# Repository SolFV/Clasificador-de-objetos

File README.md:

# 🏭 Clasificador Automático de Cajas con Visión Artificial
### Proyecto 4: Interfaz de Usuario y Estructura Mecánica de Cinta Transportadora

<div align="center">

**Sistema mecatrónico embebido de inspección de calidad y clasificación automatizada de paquetes sobre cinta transportadora, integrando visión artificial en la nube, tracción controlada por motor paso a paso, almacenamiento de evidencias y dashboard de supervisión en tiempo real.**

*Facultad de Ingeniería — Universidad Nacional de Asunción (FIUNA)*  
*Cátedra: Proyecto 4 (2do Ciclo 2026) | Septiembre de 2026*  
*Profesores: Prof. Ing. Federico Gaona, MSc. (Teoría) — Prof. Ing. Esteban Fretes, MSc. (Práctica)*

</div>

---

## 📋 Tabla de Contenidos

- [Descripción General](#-descripción-general)
- [Estado del Proyecto — Hitos del 1er Parcial](#-estado-del-proyecto--hitos-del-1er-parcial)
- [Esquema General del Sistema](#-esquema-general-del-sistema)
- [Arquitectura de Hardware](#️-arquitectura-de-hardware)
  - [1. Subsistema Mecánico y Estructura (SolidWorks)](#1-subsistema-mecánico-y-estructura-solidworks)
  - [2. Subsistema de Tracción (NEMA 23 + L298N)](#2-subsistema-de-tracción-nema-23--l298n)
  - [3. Subsistema Electrónico de Control (PCB ESP32-S3)](#3-subsistema-electrónico-de-control-pcb-esp32-s3)
- [Flujo de Operación y Lógica de Clasificación](#-flujo-de-operación-y-lógica-de-clasificación)
- [Infraestructura IoT y Servidor de Visión (n8n)](#-infraestructura-iot-y-servidor-de-visión-n8n)
- [Interfaz de Usuario (Dashboard de Supervisión)](#-interfaz-de-usuario-dashboard-de-supervisión)
- [Resultados Experimentales del Parcial](#-resultados-experimentales-del-parcial)
- [Costos del Proyecto](#-costos-del-proyecto)
- [Estructura del Repositorio](#-estructura-del-repositorio)
- [Autores y Agradecimientos](#-autores-fiuna--2026)
- [Licencia](#-licencia)

---

## 📖 Descripción General

El proyecto resuelve el **control de calidad en líneas de empaquetado** mediante un prototipo mecatrónico accesible y modular: una cinta transportadora desplaza cajas frente a una estación de inspección óptica (sensor infrarrojo de proximidad y cámara digital), un agente de visión artificial dictamina el estado del empaque y el sistema registra la evidencia fotográfica en la nube a la vez que acciona un mecanismo deflector para separar los productos defectuosos.

El alcance del **Primer Parcial del Proyecto 4** cierra la brecha entre la electrónica fabricada previamente en el Proyecto 3 y la operación física en planta, dotando al clasificador de:
1. **Estructura mecánica formal:** Chasis, rodillos, banda de caucho y soportes diseñados en SolidWorks con planos constructivos acotados.
2. **Tracción precisa con motor paso a paso:** Sustitución del motor DC de tracción por un motor paso a paso **NEMA 23** con controlador dedicado **L298N**, logrando un avance controlado con paradas repetibles de **1,2 s** frente a la cámara para eliminar el desenfoque por movimiento (*motion blur*).
3. **Pipeline de visión en la nube:** Servidor autoalojado **n8n** que procesa la imagen con **OpenAI `gpt-4o-mini`**, almacena evidencias en **Google Drive** y registros numéricos en **Google Sheets**.
4. **Dashboard web en tiempo real:** Interfaz de supervisión que lee la hoja de resultados cada 10 segundos, mostrando métricas, miniaturas de las cajas inspeccionadas y exportación a CSV.

---

## ✅ Estado del Proyecto — Hitos del 1er Parcial

> **El Primer Parcial del Proyecto 4 ha sido completado y validado experimentalmente con éxito en laboratorio.**

### Matriz de Hitos (P4 — Primer Parcial):

| Hito / Entregable | Estado | Observación |
| :--- | :---: | :--- |
| **Diseño mecánico en SolidWorks (CAD 3D)** | ✅ Completado | Modelos de bastidor, rodillos, engranajes y ensamble completo (`Ensamble.SLDASM`). |
| **Planos técnicos acotados de fabricación** | ✅ Completado | Planos 2D en PDF de engranaje conductor, conducido, soporte lateral y ensamble general. |
| **Tracción paso a paso NEMA 23 + L298N** | ✅ Completado | Paradas programadas de 1,2 s y avance exacto sin deslizamiento. |
| **Transmisión por engranajes rectos (3.8:1)** | ✅ Completado | Impresión 3D en PLA de piñón (z=10) y corona (z=38), módulo 4 mm. |
| **Flujo de Visión n8n + GPT-4o-mini** | ✅ Completado | Inferencia visual remota con latencia de 2,5 a 4,0 s. |
| **Registro Cloud (Google Drive + Sheets)** | ✅ Completado | Almacenamiento automático de fotos y fila de metadatos por evento. |
| **Dashboard Web de Supervisión** | ✅ Completado | Actualización continua cada 10 s, KPIs por estado, visor fotográfico y exportación CSV. |
| **Ensamble y validación del prototipo físico** | ✅ Completado | Estructura de contrachapado y varillas DIN 975 operativa y verificada en banco. |

---

## 🗺️ Esquema General del Sistema

El sistema opera mediante la interacción coordinada de cinco bloques funcionales:

```
                  +-------------------------------------------------------------+
                  |                      UNIDAD DE CONTROL                      |
                  |                Placa Propia ESP32-S3 (3.3V)                 |
                  +--------------+------------------------------+---------------+
                                 |                              |
               Señal de Detención|                              |Control de Desvío
               y Pulsos de Avance|                              |Pulsos PWM (0° / 180°)
                                 v                              v
            +--------------------+---------+          +---------+--------------------+
            |      SUBSISTEMA TRACCIÓN     |          |       SUBSISTEMA DESVÍO      |
            |     Driver L298N + NEMA 23   |          |    Servomotor SER0006        |
            |  Engranajes PLA (Red. 3.8:1) |          | Brazo Deflector (20s retenc.)|
            +--------------------+---------+          +------------------------------+
                                 |
                                 v
                     [ Cinta Transportadora ] <=== [ Cajas en Tránsito ]
                                 |
                          Detección IR (E18-D80NK)
                          Captura Foto (OV5640 SVGA)
                                 |
                                 v WiFi (HTTP POST Webhook)
            +--------------------+---------------------------------------------------+
            |                     SERVIDOR DE VISIÓN (n8n Autoalojado)               |
            |             Agente IA de Visión (OpenAI gpt-4o-mini)                  |
            +--------------------+------------------------------+--------------------+
                                 |                              |
                   Guarda Foto   v                 Guarda Fila  v
                         +-------+-------+              +-------+-------+
                         | Google Drive  |              | Google Sheets |
                         +-------+-------+              +-------+-------+
                                 |                              |
                                 |            Lectura cada 10 s |
                                 +--------------+---------------+
                                                v
                                 +--------------+---------------+
                                 |     DASHBOARD WEB (GUI)      |
                                 |  Supervisión en Tiempo Real  |
                                 +------------------------------+
```

---

## 🛠️ Arquitectura de Hardware

### 1. Subsistema Mecánico y Estructura (SolidWorks)
La cinta transportadora se diseñó íntegramente en SolidWorks bajo criterios de rigidez, repetibilidad y desmontaje modular:
- **Bastidor Lateral (`Tabla.SLDPRT` / [Soporte Lateral.pdf](Hardware/Diseno_Mecanico/Soporte%20Lateral.pdf)):** 2 placas de madera contrachapada de $700 \times 150\text{ mm}$ y $12\text{ mm}$ de espesor con perforaciones para varillas y rodamientos.
- **Tirantes Transversales (`Varilla.SLDPRT`):** 7 varillas roscadas de acero al carbono galvanizado bajo norma **DIN 975** (M6), aportando alta rigidez torsional.
- **Banda de Transporte (`Cinta.SLDPRT`):** Banda cerrada de caucho continuo con ancho útil de **200 mm**, compatible con cajas de hasta 150 mm.
- **Transmisión por Engranajes Rectos en PLA (Módulo 4 mm):**
  - **Engranaje Conductor (`Engranaje_C.SLDPRT` / [Engranaje_Conductor.pdf](Hardware/Diseno_Mecanico/Engranaje_Conductor.pdf)):** $z_1 = 10\text{ dientes}$, diámetro exterior $\varnothing 48.00\text{ mm}$, acople a eje del motor NEMA 23 de $\varnothing 8.00\text{ mm}$.
  - **Engranaje Conducido (`engranaje_G.SLDPRT` / [engranaje_conducido.PDF](Hardware/Diseno_Mecanico/engranaje_conducido.PDF)):** $z_2 = 38\text{ dientes}$, diámetro exterior $\varnothing 160.00\text{ mm}$, acople a eje motriz de $\varnothing 6.00\text{ mm}$.
  - **Relación de Reducción:** $i = 3.8:1$, cuadruplicando el par sobre el rodillo motriz y permitiendo una resolución de avance lineal de $\approx 0.165\text{ mm/paso}$.
- **Planos Técnicos:** Disponibles en [Hardware/Diseno_Mecanico/](Hardware/Diseno_Mecanico/) con el ensamble general en [Cinta transportadora.pdf](Hardware/Diseno_Mecanico/Cinta%20transportadora.pdf) y el informe técnico detallado en [Informe_Diseno_Estructural_Mecanico.md](Hardware/Diseno_Mecanico/Informe_Diseno_Estructural_Mecanico.md).

### 2. Subsistema de Tracción (NEMA 23 + L298N)
- **Motor:** Paso a paso híbrido bipolar NEMA 23 (**modelo 23HS5628**), ángulo de paso $1.8^\circ$ (200 pasos/rev) y torque nominal de **12.6 kgf-cm** (1.23 N·m).
- **Controlador:** Driver tipo puente H bipolar **L298N**, alimentado desde una línea de potencia externa dedicada y comandado por señales lógicas de 3.3V desde la placa ESP32-S3.

### 3. Subsistema Electrónico de Control (PCB ESP32-S3)
Se reutiliza la placa desarrollada y validada en el Proyecto 3 (alojada en [Hardware/Diseño final p3/](Hardware/Diseño%20final%20p3/)):
- **Microcontrolador:** ESP32-S3-WROOM-1-N16R8 (Dual-core 240 MHz, 16 MB Flash, 8 MB PSRAM verificada).
- **Cámara Óptica:** Módulo digital Omnivision **OV5640** conectado mediante interfaz de video en paralelo DVP (resolución de trabajo SVGA $800 \times 600$).
- **Sensor de Presencia:** Sensor fotoeléctrico infrarrojo **E18-D80NK** enfocado a la zona de captura (tiempo de respuesta $< 50\text{ ms}$).
- **Actuador de Desvío:** Servomotor **DFRobot SER0006** montado con brazo deflector mecánico a la salida del tramo de inspección.

---

## 🔄 Flujo de Operación y Lógica de Clasificación

El lazo de control opera de acuerdo a la siguiente secuencia automática:

1. **Avance Continuo:** El motor NEMA 23 hace avanzar la cinta transportadora de manera uniforme.
2. **Detección Frontal:** El sensor infrarrojo E18-D80NK detecta la llegada del paquete e interrumpe el avance.
3. **Parada y Captura:** La cinta se detiene exactamente durante **1,2 segundos**. La cámara OV5640 toma una fotografía nítida en SVGA almacenándola en la PSRAM.
4. **Transmisión IoT:** El ESP32-S3 envía la imagen por WiFi al webhook de n8n mediante HTTP POST.
5. **Inferencia Visual:** El agente de IA (`gpt-4o-mini`) analiza la morfología y condiciones del empaque, dictaminando la categoría:
   - 🟢 **Verde (Buen Estado):** Caja intacta, correctamente sellada y lista para despacho.
   - 🟡 **Amarillo (Sin Caja o No Empaque):** Falsa alarma, objeto extraño o cinta vacía.
   - 🔴 **Rojo (Caja Dañada):** Paquete aplastado, roto, perforado o con defectos visibles.
6. **Almacenamiento Cloud:** El flujo guarda la imagen en una carpeta compartida de **Google Drive** y registra una nueva fila en **Google Sheets** con timestamp, color y descripción detallada.
7. **Acción del Servomotor:** El ESP32-S3 recibe la respuesta `[{color, descripcion}]` y ejecuta la maniobra:
   - 🟢 **Verde:** El brazo deflector permanece a **0°** (la caja continúa sin desvío).
   - 🟡 / 🔴 **Amarillo o Rojo:** El servomotor gira a **180°** y mantiene la posición de desvío durante **20 segundos** para enviar la pieza a la bandeja de rechazo.
8. **Reanudación:** El servomotor retorna a posición neutra (0°) y la cinta reanuda la marcha.

---

## 🤖 Infraestructura IoT y Servidor de Visión (n8n)

El procesamiento cognitivo se delega íntegramente a un servidor local **n8n autoalojado** (*Workflow Proyecto 4*):

```
[Webhook HTTP] ──▶ [Recibir imagen y Nombrar] ──▶ [Base64 a Binario] ──▶ [AI Agent (gpt-4o-mini)]
                                                                                │
[Responder al Webhook: {color, desc}] ◀── [Limpiar Output Agente] ◀─────────────┘
          │
          ├──▶ [Subir a Google Drive]
          └──▶ [Subir a Google Sheets]
```

- **Modelo de Inferencia:** OpenAI `gpt-4o-mini` configurado con *system prompt* especializado en control de calidad industrial.
- **Respuesta JSON:** Formato estandarizado `[ { "color": "verde" | "amarillo" | "rojo", "descripcion": "..." } ]`.
- **Ventaja de la Arquitectura:** Libera al microcontrolador de tareas pesadas de redes neuronales, acelerando la toma de decisiones ($2.5 - 4.0\text{ s}$).

---

## 🖥️ Interfaz de Usuario (Dashboard de Supervisión)

El monitoreo del sistema se realiza a través de un **Dashboard Web en Tiempo Real** de un solo archivo:
- **Consulta Automática:** Sondea la planilla de Google Sheets (*Proyecto4 - Hoja 1*) cada **10 segundos**.
- **Panel de KPIs:** Conteo total de cajas evaluadas, desglose por categoría (verde, amarillo, rojo) y cálculo porcentual.
- **Tarjeta de Última Detección:** Muestra la fotografía en miniatura cargada desde Google Drive, el estado asignado, la descripción diagnóstica de la IA y el ángulo/tiempo aplicado por el servomotor.
- **Historial y Exportación:** Tabla con las últimas 5 detecciones en vivo y botón para exportar todo el registro histórico acumulado a formato **CSV**.
- **Accesos Directos:** Enlaces directos a la planilla en línea y a la carpeta de evidencias en Drive.
- **Modo Seguro:** Opera en modo solo lectura para supervisión remota sin interferir en la máquina de estados del firmware.

---

## 📊 Resultados Experimentales del Parcial

Durante las pruebas funcionales del prototipo integrado se validaron las siguientes métricas de desempeño:

| Parámetro Operativo | Valor Medido | Valor Esperado / Criterio |
| :--- | :---: | :---: |
| **Tiempo de parada de cinta frente a cámara** | **1,2 s** | Repetible, sin desenfoque de imagen |
| **Latencia de detección del sensor IR** | **< 50 ms** | Detención instantánea del NEMA 23 |
| **Tiempo de respuesta inferencia n8n** | **2,5 a 4,0 s** | Dentro del ciclo de cinta previsto |
| **Retención del servomotor en rechazo (180°)** | **20 s** | Desvío seguro al contenedor de descarte |
| **Frecuencia de actualización del Dashboard** | **10 s** | Supervisión fluida de métricas Cloud |
| **Resolución cinemática de la cinta** | **~0,165 mm/paso** | Posicionamiento milimétrico repetible |

---

## 💰 Costos del Proyecto

La estructura de costos del prototipo se basa en una tasa oficial de referencia de **1 USD = 6.391 Gs.**:

### 1. Materiales y Herramientas Compradas (Incorporadas al Proyecto 4)

| Descripción / Componente | MPN / Modelo | Cant. | Unitario (USD) | Total (USD) | Total (Gs.) |
| :--- | :--- | :---: | :---: | :---: | :---: |
| **Motor paso a paso NEMA 23 (12.6 kgf-cm)** | 23HS5628 | 1 | 46,94 | 46,94 | 300.000 |
| **Microcontrolador ESP32-S3** | ESP32-S3-WROOM-1-N16R8 | 2 | 8,72 | 17,44 | 111.459 |
| **Módulo de cámara OV5640** | 5840 (Adafruit) | 1 | 9,95 | 9,95 | 63.590 |
| **Capacitor electrolítico 100 uF** | EEE-FK1H101P | 6 | 0,76 | 4,56 | 29.143 |
| **Servomotor 180°** | SER0006 | 1 | 3,63 | 3,63 | 23.199 |
| **Capacitor cerámico 4,7 uF 0805** | CL21B475KOFNNNE | 6 | 0,25 | 1,50 | 9.587 |
| **Diodo Schottky 40 V, 1 A** | SS14F-HF | 4 | 0,32 | 1,28 | 8.180 |
| **Conector USB tipo C hembra** | USB4510-03-1-A | 1 | 0,84 | 0,84 | 5.368 |
| **Capacitor cerámico 10 uF 0805** | CL21B106KOQNNNE | 6 | 0,14 | 0,84 | 5.368 |
| **Capacitor cerámico 22 uF 0805** | CL21A226MQQNNNE | 6 | 0,13 | 0,78 | 4.985 |
| **Resistencia 15 kOhm 0805** | RC0805FR-0715KL | 6 | 0,13 | 0,78 | 4.985 |
| **Capacitor cerámico 2,2 uF 0805** | CL21B225KOFNNNE | 6 | 0,12 | 0,72 | 4.602 |
| **Regulador LDO 3,3 V** | LD1117S33TR | 2 | 0,34 | 0,68 | 4.346 |
| **Resistencia 10 kOhm 0805** | RC0805FR-0710KL | 6 | 0,11 | 0,66 | 4.218 |
| **Capacitores y Resistencias SMD 0805 varios** | Pasivos estándar | — | — | 6,14 | 39.299 |
| **SUBTOTAL COMPONENTES COMPRADOS** | — | — | — | **$96,06** | **644.219 Gs.** |

> *Costo por integrante (3 personas): **$32.02 USD (214.740 Gs.)**.*  
> El desglose línea a línea con enlaces y números de parte se encuentra en el archivo [BOM.csv](BOM.csv).

### 2. Materiales y Herramientas Preexistentes o Prestadas (Sin costo incremental)

| Descripción | Cantidad | Observaciones / Procedencia |
| :--- | :---: | :--- |
| **Placa propia ESP32-S3 con cámara OV5640** | 1 | Fabricada y validada en Proyecto 3 |
| **Servomotor de desvío SER0006** | 1 | Reutilizado de la etapa previa |
| **Controlador L298N para motor paso a paso** | 1 | Driver provisto para tracción |
| **Notebook con servidor n8n autoalojado** | 1 | Estación de inferencia local |
| **Licencia / estación SolidWorks CAD** | 1 | Laboratorio FIUNA |
| **Multímetro y herramientas de banco/taller** | 1 | Instrumental de ensamblaje y prueba |

---

## 📁 Estructura del Repositorio

```
📦 Clasificador de Objetos/
├── 📂 Hardware/                                # Proyectos de diseño físico y electrónico
│   ├── 📂 Diseno_Mecanico/                     # Diseño mecánico CAD y planos (P4)
│   │   ├── 📄 Informe_Diseno_Estructural_Mecanico.md # Informe técnico mecánico detallado
│   │   ├── 📄 Cinta transportadora.pdf         # Plano de ensamble general, despiece y lista de partes
│   │   ├── 📄 Soporte Lateral.pdf              # Plano acotado de soporte lateral de madera contrachapada
│   │   ├── 📄 Engranaje_Conductor.pdf          # Plano acotado de engranaje conductor (z=10, m=4)
│   │   ├── 📄 engranaje_conducido.PDF          # Plano acotado de engranaje conducido (z=38, m=4)
│   │   ├── 🧊 Ensamble.SLDASM                  # Ensamblaje 3D general en SolidWorks
│   │   ├── 🧊 Cinta.SLDPRT                     # Modelo 3D de la banda transportadora
│   │   ├── 🧊 Engranaje_C.SLDPRT               # Modelo 3D de engranaje conductor (PLA)
│   │   ├── 🧊 engranaje_G.SLDPRT               # Modelo 3D de engranaje conducido (PLA)
│   │   ├── 🧊 Tabla.SLDPRT                     # Modelo 3D de soporte lateral
│   │   ├── 🧊 Varilla.SLDPRT                   # Modelo 3D de varilla roscada DIN 975
│   │   └── 🧊 nema23.SLDPRT                    # Modelo 3D de motor paso a paso NEMA 23
│   ├── 📂 Componentes/                         # Bibliotecas KiCad personalizadas
│   ├── 📂 Diseño final p3/                     # Proyecto final KiCad de la PCB (Proyecto 3)
│   │   └── 📂 Grupo15/                         # Esquemático, ruteado, producción y Gerbers
│   ├── 📂 ESP32_S3_WROOM2_N32R16_29/           # Footprint y símbolo de la MCU
│   ├── 🖼️ Diseño.jpeg                          # Esquemático general del circuito
│   ├── 🖼️ pcb_ruteado.PNG                       # Ruteado y layout de 2 capas
│   ├── 🖼️ pcb_3d.PNG                           # Render 3D superior de la PCB
│   ├── 🖼️ pcb_3d_1.png                         # Render 3D superior sin componentes
│   └── 🖼️ pcb_3d_vistinferior.png              # Render 3D inferior de la PCB
├── 📂 Software/                                # Firmware y aplicaciones de control
│   ├── 📄 P3_2P_code.txt                       # Firmware C++/Arduino para ESP32-S3
│   ├── 📂 SnapshotP4.0/                        # Aplicación Android para inspección
│   │   └── 📱 Cinta IA.apk                     # Instalador ejecutable Android
│   └── 📂 Pruebas/                             # Scripts de validación de cámara y PSRAM
├── 📄 BOM.csv                                  # Lista de materiales y costos actualizada (USD / Gs.)
├── 📄 Informe_finalP3.pdf                      # Informe oficial completo del Proyecto 3
├── 📄 Cronograma de actividades P4.pdf         # Cronograma oficial de la Etapa P4 (PDF)
├── 📊 Cronograma de actividades.xlsx           # Planilla Excel de seguimiento
├── 🖼️ DiagramadeGantt.png                     # Diagrama de Gantt oficial
├── 🖼️ diagrama-flujo.png                       # Diagrama de flujo general del sistema
├── 📄 LICENSE                                  # Licencia de código abierto MIT
└── 📄 README.md                                # Documentación principal del repositorio
```

---

## 👥 Autores (FIUNA — 2026)

* **José Fabián Medina Dávalos** — [jfmedina@fiuna.edu.py](mailto:jfmedina@fiuna.edu.py)
* **Sol Aramí Fernández Vargas** — [solfernandez@fiuna.edu.py](mailto:solfernandez@fiuna.edu.py)
* **Gabriela Belén Orrego Arzamendia** — [gorrego@fiuna.edu.py](mailto:gorrego@fiuna.edu.py)

**Facultad de Ingeniería — Universidad Nacional de Asunción (FIUNA)**  
*Cátedra de Proyecto 4 — Carrera de Ingeniería Mecatrónica*  
*Docentes:* Prof. Ing. Federico Gaona, MSc. (Teoría) & Prof. Ing. Esteban Fretes, MSc. (Práctica)

---

## 📄 Licencia

Este proyecto está distribuido bajo la **Licencia MIT**. Para más detalles, consulte el archivo [LICENSE](LICENSE).

---

<div align="center">

*Clasificador Automático de Cajas con Visión Artificial — FIUNA — 2026*

</div>

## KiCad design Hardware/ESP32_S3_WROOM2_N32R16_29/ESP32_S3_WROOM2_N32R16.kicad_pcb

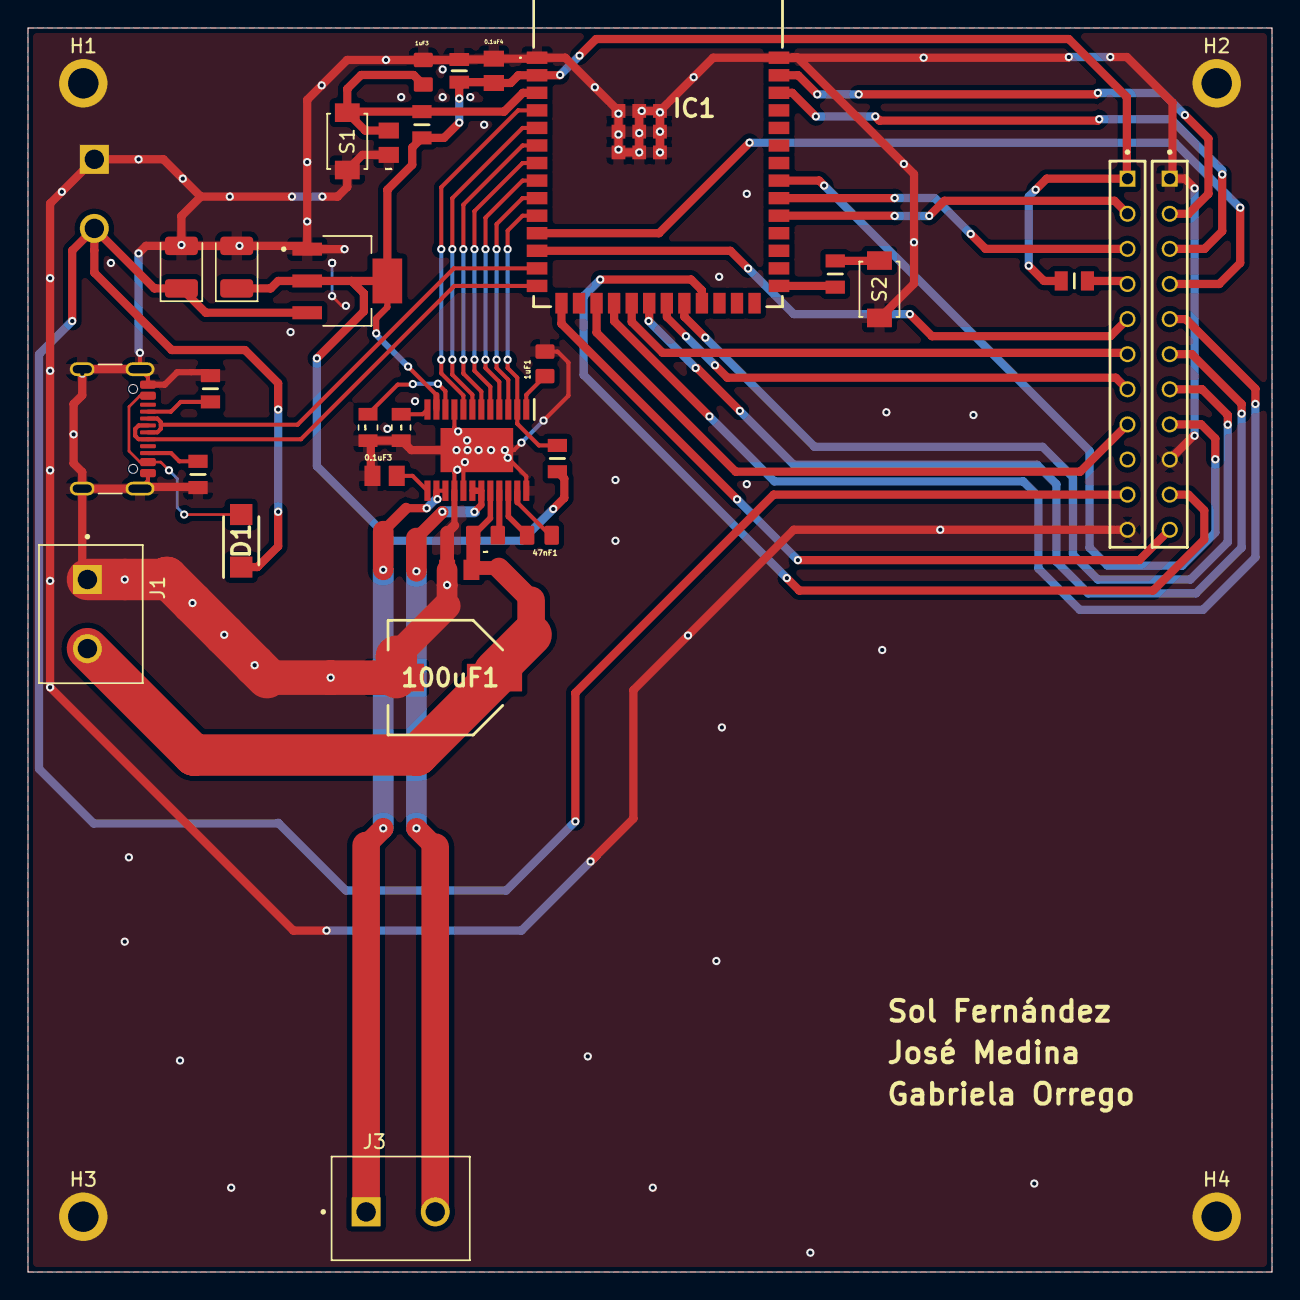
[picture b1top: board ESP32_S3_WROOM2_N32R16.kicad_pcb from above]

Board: 2 copper layers, 90.0 x 90.0 mm, 36 parts (1 on the bottom side), 44 nets.

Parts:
0.1k1: RC0805FR-07100RL; RESC2012X60N
0.1uF1, 0.1uF2, 0.1uF3, 0.1uF4: 08055C104KAT2A; CAPC2012X94N
1.5k1, 1.5k2: RC0805FR-071K5L; RESC2012X60N
1uF1, 1uF2, 1uF3: CL21B105KAFNNNE; CAPC2012X135N
5.1k1, 5.1k2: RK73H2ATTD5101F; RESC2012X60N
10k1, 10k2, 10k3: RC0805FR-0710KL; RESC2012X60N
22uF1: CL21A226MQQNNNE; CAPC2012X140N
47nF1: CL21B473KBCNNNC; CAPC2012X95N
100uF1: EEE-FK1H101P; EEHZT1E331UP
C1, C2: 10uF; CP_EIA-3528-21_Kemet-B
D1: SS14F-HF; SODFL4626X120N
H1, H2, H3, H4: MountingHole_2.2mm_M2_ISO7380_Pad
H1#2: DRV8873SPWPRQ1; SOP65P640X120-25N
IC1: ESP32-S3-WROOM-2-N32R16V; ESP32S3WROOM2N32R16V
J1, J2, J3: KF301-2P; HANDSON_KF301-2P
J4, J5: TS-111-T-A-1; SAMTEC_TS-111-T-A-1
S1, S2: TS-1088-AR02016; SW_TS-1088-AR02016
USB1: USB_C_Receptacle_USB2.0_16P; USB_C_Receptacle_GCT_USB4105-xx-A_16P_TopMnt_Horizontal
VR1: LM1117MPX-3.3_NOPB; VREG_LM1117MPX-3.3_NOPB

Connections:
+3V3: 0.1uF4.2, 10k1.2, 10k2.2, 10k3.2, 22uF1.2, C2.1, H1#2.11 (NSLEEP), IC1.2 (3V3), J5.01, VR1.2 (VOUT_2), VR1.4 (VOUT_4)
+5V: C1.1, D1.1 (K), J2.2, J5.10, VR1.3 (VIN)
BOOT: 0.1k1.1, IC1.27 (IO0)
D+: IC1.14 (IO20), USB1.A6 (D+), USB1.B6 (D+)
D-: IC1.13 (IO19), USB1.A7 (D-), USB1.B7 (D-)
EN: 0.1uF1.1, 1uF3.2, 10k2.1, IC1.3 (EN), S1.1
GND: 0.1uF1.2, 0.1uF2.1, 0.1uF3.1, 0.1uF4.1, 1.5k1.1, 1.5k2.1, 1uF1.2, 1uF3.1, 5.1k1.2, 5.1k2.2, 22uF1.1, 100uF1.2 (-), C1.2, C2.2, H1.1, H1#2.9 (DISABLE), H1#2.16 (SRC_1), H1#2.17 (SRC_2), H1#2.24 (GND), H1#2.25 (EP), H2.2, H3.3, H4.4, IC1.1 (GND_1), IC1.40 (GND_2), IC1.41 (GND_3), IC1.42 (GND_4), IC1.43 (GND_5), IC1.44 (GND_6), IC1.45 (GND_7), IC1.46 (GND_8), IC1.47 (GND_9), IC1.48 (GND_10), IC1.49 (GND_11), J1.1, J2.1, J4.01, J4.09, J5.11, S1.2, S2.2, USB1.A1 (GND), USB1.A12 (GND), USB1.B1 (GND), USB1.B12 (GND), USB1.SH (SHIELD), VR1.1 (GND)
GPIO01: IC1.39 (IO1), J4.02
GPIO02: IC1.38 (IO2), J4.03
GPIO03: IC1.15 (IO3), J4.11
GPIO04: H1#2.8 (PH/IN2), IC1.4 (IO4)
GPIO05: H1#2.7 (EN/IN1), IC1.5 (IO5)
GPIO06: H1#2.6 (NSCS), IC1.6 (IO6)
GPIO07: H1#2.5 (SCLK), IC1.7 (IO7)
GPIO08: IC1.12 (IO8), J5.05
GPIO09: IC1.17 (IO9), J5.08
GPIO10: IC1.18 (IO10), J4.05
GPIO11: IC1.19 (IO11), J5.06
GPIO12: IC1.20 (IO12), J4.06
GPIO13: IC1.21 (IO13), J5.07
GPIO14: IC1.22 (IO14), J4.07
GPIO15: H1#2.4 (SDI), IC1.8 (IO15)
GPIO16: H1#2.3 (SDO), IC1.9 (IO16)
GPIO17: 10k1.1, H1#2.2 (NFAULT), IC1.10 (IO17)
GPIO18: IC1.11 (IO18), J4.04
GPIO21: IC1.23 (IO21), J4.10
GPIO38: IC1.31 (IO38), J5.02
GPIO39: IC1.32 (IO39), J5.03
GPIO40: IC1.33 (IO40), J4.08
unnamed: 0.1k1.2, S2.1
unnamed: 10k3.1, J5.04
unnamed: D1.2 (A), USB1.A4 (VBUS), USB1.A9 (VBUS), USB1.B4 (VBUS), USB1.B9 (VBUS)
unnamed: 47nF1.2, H1#2.22 (CPH)
unnamed: 47nF1.1, H1#2.23 (CPL)
unnamed: 1uF1.1, H1#2.1 (DVDD)
unnamed: 1.5k2.2, H1#2.10 (IPROPI1)
unnamed: 1.5k1.2, H1#2.12 (IPROPI2)
unnamed: 1uF2.2, H1#2.21 (VCP)
unnamed: 0.1uF3.2, H1#2.13 (VM_1)
unnamed: 5.1k2.1, USB1.A5 (CC1)
unnamed: 5.1k1.1, USB1.B5 (CC2)
O1: H1#2.18 (OUT1_1), H1#2.19 (OUT1_2), J3.2
O2: H1#2.14 (OUT2_1), H1#2.15 (OUT2_2), J3.1
VM: 0.1uF2.2, 1uF2.1, 100uF1.1 (+), H1#2.20 (VM_2), J1.2

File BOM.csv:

,,,,,,,,
,,,,Dolar,6538,,,
,Total,414.434,Individual,138.145,,,,
,Categoría,Componente,Marca,Precio USD,Precio PYG,Link,Cant. Mín,Precio Final PYG
,MCU,ESP32-S3-WROOM-2-N32R16V,Espressif Systems,"11,40",74.533,https://www.mouser.com/ProductDetail/Espressif-Systems/ESP32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,1,74.533
,MOTOR,"NOVAMAX-6V-5,75A-800RPM",Sumozade,"15,00",98.070,https://sumozade.com/novamax-6v-800rpm-dc-motor,1,98.070
,LDO,LM1117MPX-3.3/NOPB,Diodes Incorporated,"1,04",6.800,https://www.mouser.com/ProductDetail/Texas-Instruments/LM111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,2,13.599
,DRIVER,DRV8873SPWPRQ1,Texas Instruments,"4,13",27.002,https://www.mouser.com/ProductDetail/Texas-Instruments/DRV88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,2,54.004
,CAMERA, OV5640 DVP,CN,"10,04",64.789,https://es.aliexpress.com/item/1005004471654205.html?dp=gx-r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,2,129.578
,USB-C,USB TIPO C HEMBRA 16 PINES 1.6MM SMD,Plett,"2,30",15.037,CONECTOR USB TIPO C HEMBRA 16 PINES 1.6MM SMD - Electronica Plett,1,15.037
,COMPONENTES,,,,,,,
,Capacitor de Tantalio 10uF,T491B106K016AT,KEMET,"0,44",2.877,https://www.mouser.com/ProductDetail/KEMET/T491B106K016AT?qs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,2,5.753
,Capacitor Ceramico 1uF,CL21B105KAFNNNE,Samsung Electro-Mechanics,"0,11",719,https://www.mouser.com/ProductDetail/Samsung-Electro-Mechani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,2,1.438
,"Capacitor Ceramico 0,1uF",08055C104KAT2A,KYOCERA AVX,"0,13",850,https://www.mouser.com/ProductDetail/KYOCERA-AVX/08055C104KA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,2,1.700
,Capacitor Ceramico 22uF,CL21A226MQQNNNE,Samsung Electro-Mechanics,"0,13",839,https://www.mouser.com/ProductDetail/Samsung-Electro-Mechani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,2,1.679
,Resistencia 10k 0805,RC0805FR-0710KL,YAGEO,"0,14",915,https://www.mouser.com/ProductDetail/YAGEO/RC0805FR-0710KL?q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,2,1.831
,"Resistencia 5,1k 0805",RK73H2ATTD5101F,KOA Speer,"0,10",646,https://www.mouser.com/ProductDetail/KOA-Speer/RK73H2ATTD510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,4,2.582
,"Resistencia 0,1k 0805",RC0805FR-07100RL,YAGEO,"0,10",654,https://www.mouser.com/ProductDetail/YAGEO/RC0805FR-07100RL?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,2,1.308
,Capacitor Ceramico 47nF,CL21B473KBCNNNC,Samsung Electro-Mechanics,"0,10",646,https://www.mouser.com/ProductDetail/Samsung-Electro-Mechani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,2,1.291
,Capacitor Electrolitico 100uF,EEE-FK1H101P,Panasonic,"0,72",4.707,https://www.mouser.com/ProductDetail/Panasonic/EEE-FK1H101P?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,2,9.415
,"Resistencia 1,5k 0805",RC0805FR-071K5L,YAGEO,"0,10",654,https://www.mouser.com/ProductDetail/YAGEO/RC0805FR-071K5L?q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,4,2.615

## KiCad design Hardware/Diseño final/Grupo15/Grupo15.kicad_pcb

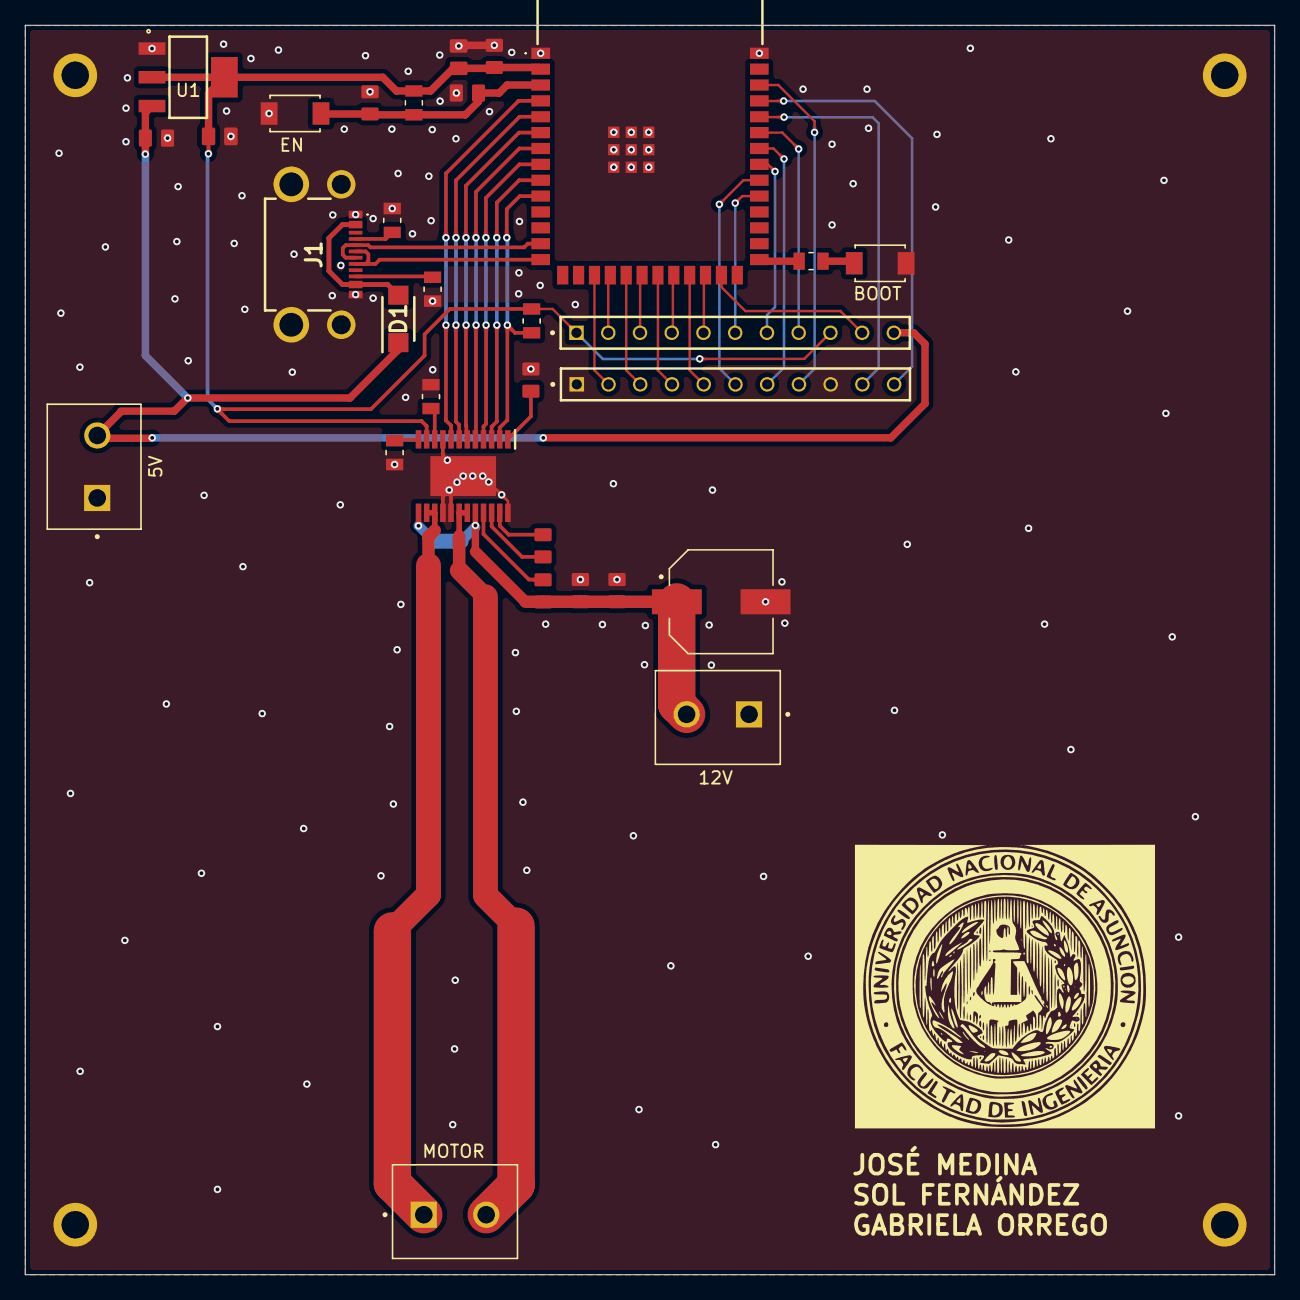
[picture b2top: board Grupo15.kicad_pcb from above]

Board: 2 copper layers, 100.0 x 100.0 mm, 35 parts (0 on the bottom side), 44 nets.

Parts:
5V, 12V: KF301-2P; HANDSON_KF301-2P
BOOT: TS-1088-AR02016; SW_TS-1088-AR02016
C1, C3, C4, C10, C11: CL21B104KBCNNNC; CAPC2012X95N
C2: CL21B106KOQNNNE; CAPC2012X140N
C5: CL21A226MQQNNNE; CAPC2012X140N
C6, C7, C9: CL21B105KAFNNNE; CAPC2012X135N
C8: CL21B473KBCNNNC; CAPC2012X95N
C12: EEEFK1H101P; CAP_EEEFK1H101P
D1: SS14F-HF; SODFL4626X120N
EN: TS-1088-AR02016; SW_TS-1088-AR02016
H1, H2, H3, H4: MountingHole_2.2mm_M2_ISO7380_Pad
H1#2: DRV8873SPWPRQ1; SOP65P640X120-25N
IC1: ESP32-S3-WROOM-1-N16R8; ESP32S3WROOM1N16R8
J1: USB4510-03-1-A; USB4510031A
J5, J6: TS-111-T-A-1; SAMTEC_TS-111-T-A-1
MOTOR: KF301-2P; HANDSON_KF301-2P
R1: RC0805FR-07100RL; RESC2012X60N
R2, R5: RC0805FR-0710KL; RESC2012X60N
R3, R4: RC0805FR-075K1L; RESC2012X60N
R6, R7: RC0805FR-071K5L; RESC2012X60N
U1: LD1117S33TR; SOT230P700X180-4N

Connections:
+3V3: C2.1, C4.1, C5.1, H1#2.11 (NSLEEP), IC1.2 (3V3), J5.01, J5.09, R2.2, R5.1, U1.2 (OUT), U1.4 (OUT)
+5V: 5V.2, C1.1, D1.1 (K), J5.11, U1.3 (IN)
BOOT: IC1.27 (IO0), R1.1
D2: IC1.38 (IO2), J6.08
D3: IC1.35 (IO42), J5.08
D4: IC1.34 (IO41), J6.07
D5: IC1.33 (IO40), J5.07
D6: IC1.32 (IO39), J6.06
D7: IC1.31 (IO38), J5.06
D8: IC1.23 (IO21), J6.05
D9: IC1.24 (IO47), J5.05
EN: C3.1, C6.1, EN.1, IC1.3 (EN), R2.1
GND: 5V.1, 12V.1, BOOT.2, C1.2, C2.2, C3.2, C4.2, C5.2, C6.2, C7.1, C10.2, C11.2, C12.2, EN.2, H1.1, H1#2.9 (DISABLE), H1#2.16 (SRC_1), H1#2.17 (SRC_2), H1#2.24 (GND), H1#2.25 (EP), H2.1, H3.1, H4.1, IC1.1 (GND_1), IC1.40 (GND_2), IC1.41 (GND_3), IC1.42 (GND_4), IC1.43 (GND_5), IC1.44 (GND_6), IC1.45 (GND_7), IC1.46 (GND_8), IC1.47 (GND_9), IC1.48 (GND_10), IC1.49 (GND_11), J1.A1 (GND_1), J1.A12 (GND_2), J1.MH1, J1.MH2, J1.MH3, J1.MH4, J6.01, J6.09, R3.1, R4.2, R6.1, R7.1, U1.1 (GND)
GPIO-04: H1#2.8 (PH/IN2), IC1.4 (IO4)
GPIO-05: H1#2.7 (EN/IN1), IC1.5 (IO5)
GPIO-06: H1#2.6 (NSCS), IC1.6 (IO6)
GPIO-07: H1#2.5 (SCLK), IC1.7 (IO7)
GPIO-15: H1#2.4 (SDI), IC1.8 (IO15)
GPIO-16: H1#2.3 (SDO), IC1.9 (IO16)
GPIO-17: H1#2.2 (NFAULT), IC1.10 (IO17), R5.2
GPIO-48: IC1.25 (IO48), J5.10
GPIO-RX: IC1.36 (RXD0), J6.10
GPIO-TX: IC1.37 (TXD0), J6.11
HS: IC1.19 (IO11), J6.03
unnamed: D1.2 (A), J1.A4 (VBUS_1), J1.A9 (VBUS_2)
unnamed: C8.2, H1#2.22 (CPH)
unnamed: C8.1, H1#2.23 (CPL)
unnamed: C7.2, H1#2.1 (DVDD)
unnamed: H1#2.10 (IPROPI1), R6.2
unnamed: H1#2.12 (IPROPI2), R7.2
unnamed: C9.1, H1#2.21 (VCP)
unnamed: J1.A5 (CC1), R3.2
unnamed: J1.B5 (CC2), R4.1
unnamed: BOOT.1, R1.2
O1: H1#2.18 (OUT1_1), H1#2.19 (OUT1_2), MOTOR.2
O2: H1#2.14 (OUT2_1), H1#2.15 (OUT2_2), MOTOR.1
PC: IC1.22 (IO14), J5.04
SCL: IC1.18 (IO10), J5.02
SDA: IC1.17 (IO9), J6.02
USB_D+: IC1.14 (IO20), J1.A6 (DP1), J1.B6 (DP2)
USB_D-: IC1.13 (IO19), J1.A7 (DN1), J1.B7 (DN2)
VM: 12V.2, C9.2, C10.1, C11.1, C12.1, H1#2.13 (VM_1), H1#2.20 (VM_2)
VS: IC1.20 (IO12), J5.03
XC: IC1.21 (IO13), J6.04

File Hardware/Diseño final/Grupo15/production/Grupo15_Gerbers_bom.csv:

Designator,Footprint,Quantity,Value,LCSC Part #
"12V, 5V, MOTOR",HANDSON_KF301-2P,3,KF301-2P,
"BOOT, EN",SW_TS-1088-AR02016,2,TS-1088-AR02016,
"C1, C10, C11, C3, C4",CAPC2012X95N,5,CL21B104KBCNNNC,
C12,CAP_EEEFK1H101P,1,EEEFK1H101P,
C2,CAPC2012X140N,1,CL21B106KOQNNNE,
C5,CAPC2012X140N,1,CL21A226MQQNNNE,
"C6, C7, C9",CAPC2012X135N,3,CL21B105KAFNNNE,
C8,CAPC2012X95N,1,CL21B473KBCNNNC,
D1,SODFL4626X120N,1,SS14F-HF,
H1_2,SOP65P640X120-25N,1,DRV8873SPWPRQ1,
IC1,ESP32S3WROOM1N16R8,1,ESP32-S3-WROOM-1-N16R8,
J1,USB4510031A,1,USB4510-03-1-A,
"J5, J6",SAMTEC_TS-111-T-A-1,2,TS-111-T-A-1,
R1,RESC2012X60N,1,RC0805FR-07100RL,
"R2, R5",RESC2012X60N,2,RC0805FR-0710KL,
"R3, R4",RESC2012X60N,2,RC0805FR-075K1L,
"R6, R7",RESC2012X60N,2,RC0805FR-071K5L,
U1,SOT230P700X180-4N,1,LD1117S33TR,

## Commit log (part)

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2026-03-28 Add links section with components list reference
2026-03-28 Update Google Sheets link in README
2026-03-28 Edit
2026-03-28 Add project report link to README
2026-03-28 Revise README for project details and specifications
    Updated project description and added detailed sections on functionality, status, features, hardware components, technologies, authors, and license.
2026-03-28 Update GitHub link for Gabriela Belén Orrego
2026-03-30 Placa pcb
2026-03-30 Componentes
2026-06-01 Revise README with current project status and details
    Updated project status, description, and hardware architecture details.
2026-06-01 Remove IoT badge from README
    Removed IoT badge from the README file.
2026-06-01 actualizacion
2026-06-01 Update README with server details and process flow
2026-06-01 Revise next steps in README for clarity
    Updated the immediate next steps section to clarify tasks related to the private server, communication, and integrated testing.
2026-06-01 Update next steps in README
    Removed the communication step for the ESP32-S3 from the next steps section.
2026-06-04 Pruebas y resultados
2026-06-05 Actualizar Resultados PSRAM.txt
2026-06-05 Actualizar Prueba PSRAM.txt
2026-06-13 Revise project title in README
    Updated project title for clarity and focus.
2026-06-13 Fix formatting of authors section in README
2026-06-13 finished
2026-06-13 Implement complete system with camera and motor control
    Updated the complete system to include camera, webhook, IR sensor, DC motor, and servo functionalities.
2026-06-13 Remove phone numbers from authors section
2026-06-13 Actualización Examen Final
2026-06-14 Refine README structure and cleaning step description
    Updated the README to clarify the final cleaning step and reorganized the project structure for better clarity.
2026-06-15 Prueba de funcionamiento
2026-06-15 error de subida
2026-06-15 evidencia de funcionamiento
